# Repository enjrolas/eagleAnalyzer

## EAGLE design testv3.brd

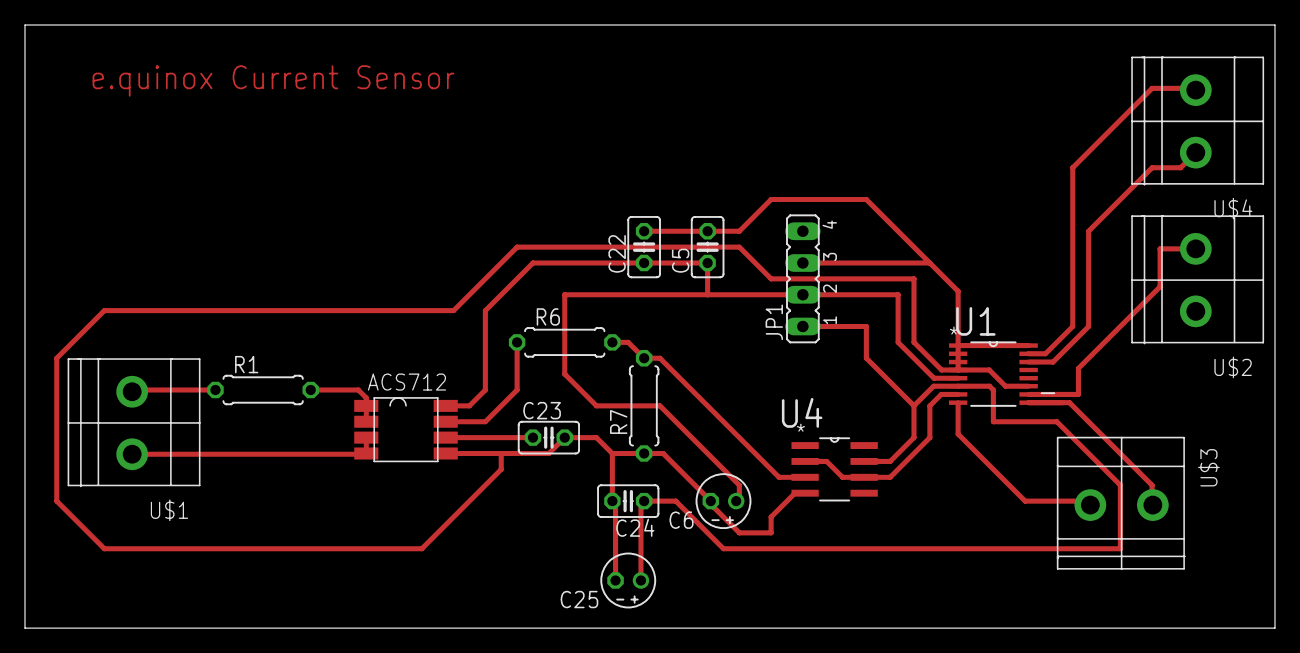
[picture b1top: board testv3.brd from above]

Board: 2 copper layers, 100.0 x 48.2 mm, 17 parts (0 on the bottom side), 15 nets.

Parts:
C5, C22, C23, C24: C025-025X050
C6, C25: E2-4
JP1: JP4
R1, R6, R7: 0207/7
U1: AD7993BRUZ-0; SOP65P640X120-16N
U4: MCP601-E/SN; SOIC127P600X175-8N
U$1, U$2, U$3, U$4: CTB1500/2; CTB1500-2
U$10: ACS712; SOIC8

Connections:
+3V3: C24.1, C25.+, JP1.1, U1.6, U4.7
+5V: C5.1, C6.+, C22.1, JP1.2, U1.5, U$10.8
GND: C5.2, C6.-, C22.2, C23.2, C24.2, C25.-, JP1.3, R7.1, U1.1, U1.2, U1.3, U1.4, U1.11, U1.16, U4.4, U$10.5
IDC_OUT: U1.7, U4.2, U4.6
unnamed: U1.9, U$3.P$1
unnamed: U1.8, U$3.P$2
unnamed: R1.1, U$1.P$2
unnamed: R1.2, U$10.1, U$10.2
unnamed: U$1.P$1, U$10.3, U$10.4
unnamed: R6.1, U$10.7
unnamed: C23.1, U$10.6
unnamed: R6.2, R7.2, U4.3
unnamed: U1.14, U$4.P$1
SCL: U1.15, U$4.P$2
VDC_OUT: U1.10, U$2.P$2

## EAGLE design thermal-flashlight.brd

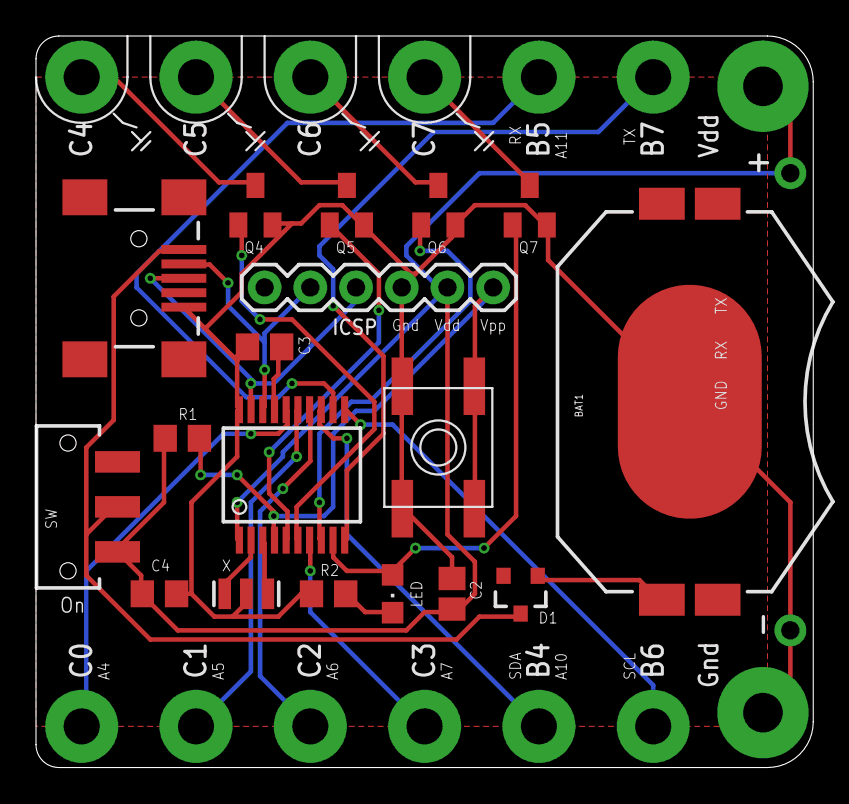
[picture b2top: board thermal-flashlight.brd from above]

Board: 2 copper layers, 43.2 x 40.6 mm, 34 parts (0 on the bottom side), 27 nets.

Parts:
BAT1: BATTCON_20MM_4LEGS
BTN: EVQ-Q2
C2: 10u; C0805
C3, C4: 0.1uF; C0805
D1: SOT23-3
ICSP: 1X06
JP+: 1X01-CLEANBIG
JP-: 1X01-CLEANBIG
LED: 0805; CHIPLED_0805
PB4: PETAL-SMALL-2SIDE1
PB5, PB6, PB7: SEWTAP6; PETAL-SMALL-2SIDE1
PC0, PC1, PC2, PC3: SEWTAP6; PETAL-SMALL-2SIDE1
PG: SEWTAP6; PETAL-SMALL-2SIDE11
PSC4, PSC5, PSC6, PSC7: SEWTAP6; PETAL-SMALL-2SIDE1
PVCC: SEWTAP6; PETAL-SMALL-2SIDE11
Q4, Q5, Q6, Q7: BSS123; SOT23
R1: 10k; R0805@1
R2: 3.3K; R0805
SW: SPDT; SWITCH-SPDT-SMD
U$1: PIC18F1X50-I/SS; SSOP20
X: 12MHz; RESONATOR-SMD
X1: USBSMD; USB-MINIB

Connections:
GND: BAT1.2, BTN.A, BTN.A', C2.2, C3.2, C4.2, ICSP.3, JP-.1, PG.1, Q4.2, Q5.2, Q6.2, Q7.2, R2.1, U$1.20, X.2, X1.GND
unnamed: U$1.2, X.1
unnamed: U$1.3, X.3
unnamed: LED.C, R2.2
PGC: ICSP.5, U$1.18, X1.D-
PGD: ICSP.4, U$1.19, X1.D+
RB4: PB4.1, U$1.13
RB5: PB5.1, U$1.12
RB6: PB6.1, U$1.11
RB7: PB7.1, U$1.10
RC0: PC0.1, U$1.16
RC1: PC1.1, U$1.15
RC2: PC2.1, U$1.14
RC3: PC3.1, U$1.7
RC4: Q4.1, U$1.6
RC5: Q5.1, U$1.5
RC6: Q6.1, U$1.8
RC7: LED.A, Q7.1, U$1.9
SC4: PSC4.1, Q4.3
SC5: PSC5.1, Q5.3
SC6: PSC6.1, Q6.3
SC7: PSC7.1, Q7.3
VBAT: BAT1.1, D1.1
VBUS: D1.3, SW.2, X1.VBUS
VDD: C2.1, C4.1, ICSP.2, JP+.1, PVCC.1, R1.2, SW.1, U$1.1
VPP: BTN.B, BTN.B', ICSP.1, R1.1, U$1.4
VUSB: C3.1, U$1.17

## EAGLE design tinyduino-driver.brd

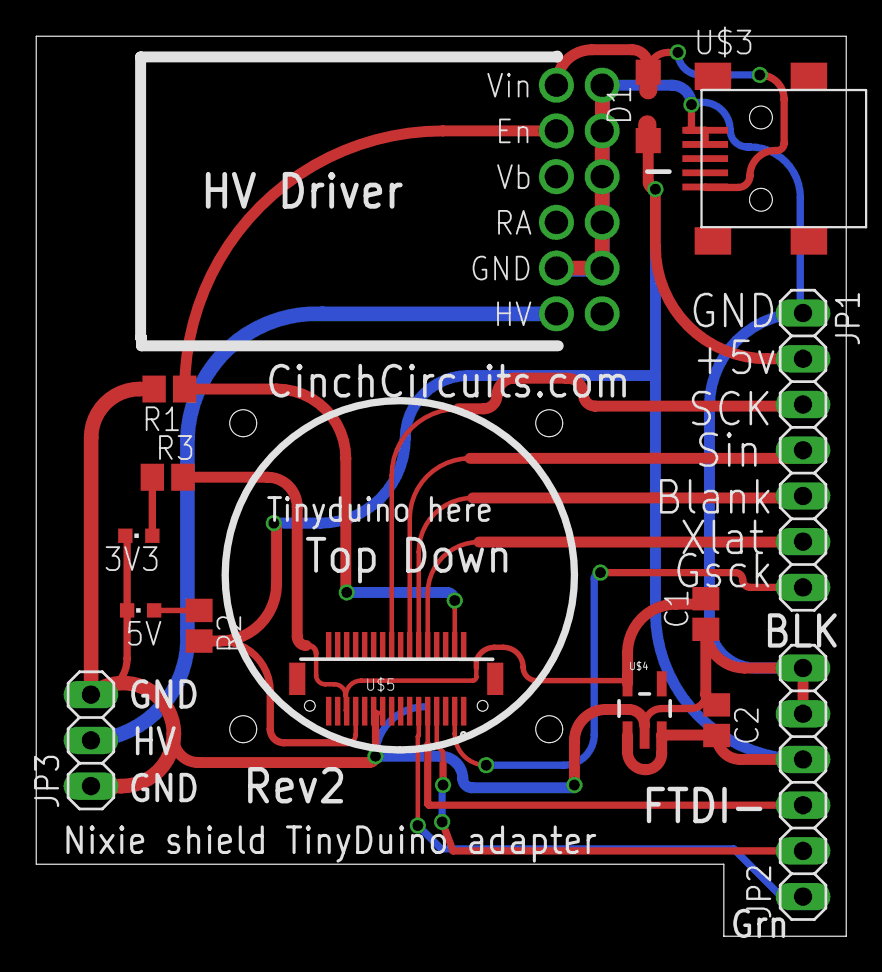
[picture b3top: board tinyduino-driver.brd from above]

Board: 2 copper layers, 45.0 x 50.0 mm, 16 parts (0 on the bottom side), 16 nets.

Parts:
3V3, 5V: CHIPLED_0603
C1, C2: C0805
D1: MBR0520LT; SOD123
JP1: 1X07
JP2: 1X06
JP3: 1X03
R1: 10k; R0805
R2, R3: R0805
U$1: DOCFIELD-TINYCIRCUITS-PCB
U$2: HV-MODULE-EBAY; NIIE-HV
U$3: USB-MICRO-SMD; CONNECTER_MINI_USB2
U$4: 3V3-LDO-TI; SOT23-5
U$5: TINYCIRCUITS-DF12-32-DS-BOTTOM; TINYCIRCUITS_DF12-32-DS

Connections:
+3V3: C1.2, R3.2, U$4.5, U$5.27
+5V: C2.2, D1.C, JP1.2, JP2.4, R2.2, U$4.1, U$4.3, U$5.25
GND: 3V3.C, 5V.C, C1.1, C2.1, JP1.1, JP2.5, JP2.6, JP3.1, JP3.3, R1.2, U$2.GND, U$2.GND1, U$2.GND2, U$2.GND4, U$2.GND5, U$2.GND6, U$3.GND0, U$3.GND1, U$4.2, U$5.19, U$5.21
HVOUT: JP3.2, U$2.HV
IO0: JP2.3, U$5.9
IO1: JP2.2, U$5.7
IO3: JP1.7, U$5.3
IO6: R1.1, U$2.ENABLE, U$5.4
IO9: JP1.6, U$5.10
MOSI: JP1.4, U$5.14
unnamed: 3V3.A, R3.1
unnamed: 5V.A, R2.1
RESET: JP2.1, U$5.11
SCK: JP1.3, U$5.18
SS: JP1.5, U$5.12
USB+5V: D1.A, U$2.VIN, U$3.VDD

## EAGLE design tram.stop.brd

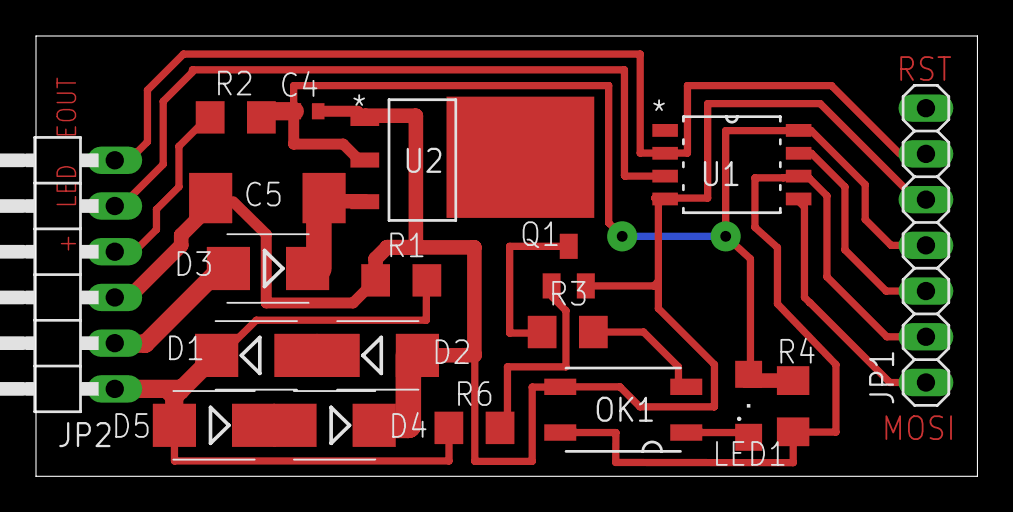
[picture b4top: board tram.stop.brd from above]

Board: 2 copper layers, 52.3 x 24.5 mm, 19 parts (0 on the bottom side), 18 nets.

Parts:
C4: 1uF; C0402
C5: SMC_D
D1, D2, D3, D4, D5: M1; SMB
JP1: 1X07
JP2: 1X06/90
LED1: KPT-3216SRD-PRV; SML1206
OK1: PC357N14; SMD4
Q1: BC847SMD; SOT23
R1: 2k2; R1206
R2, R3: 220; R1206
R4: 10K; R1206
R6: 1K; R1206
U1: ATTINY85V-10SU; SOIC127P798X216-8N
U2: LM1117MP-5.0; SOT230P696X180-4N

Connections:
220: LED1.C, OK1.1
JP1: D3.C, D5.A, JP2.1, R1.1, R6.1
JP2: C4.2, D2.A, D4.C, JP1.5, JP2.3, OK1.3, Q1.2, R1.2, U1.4, U2.1
unnamed: D2.C, D3.A
unnamed: D4.A, D5.C
unnamed: Q1.1, R6.2
unnamed: Q1.3, R3.1
unnamed: OK1.2, R3.2
unnamed: JP1.3, U1.7
unnamed: JP1.1, U1.5
unnamed: JP2.4, R2.1
unnamed: JP1.6, JP2.6
unnamed: JP1.2, OK1.4, R4.1, U1.6
unnamed: C4.1, JP1.4, LED1.A, R2.2, R4.2, U1.8, U2.2
unnamed: JP1.7, U1.1
unnamed: D1.A, JP2.2
unnamed: C5.+, D1.C, U2.3
RED2: JP2.5, U1.3

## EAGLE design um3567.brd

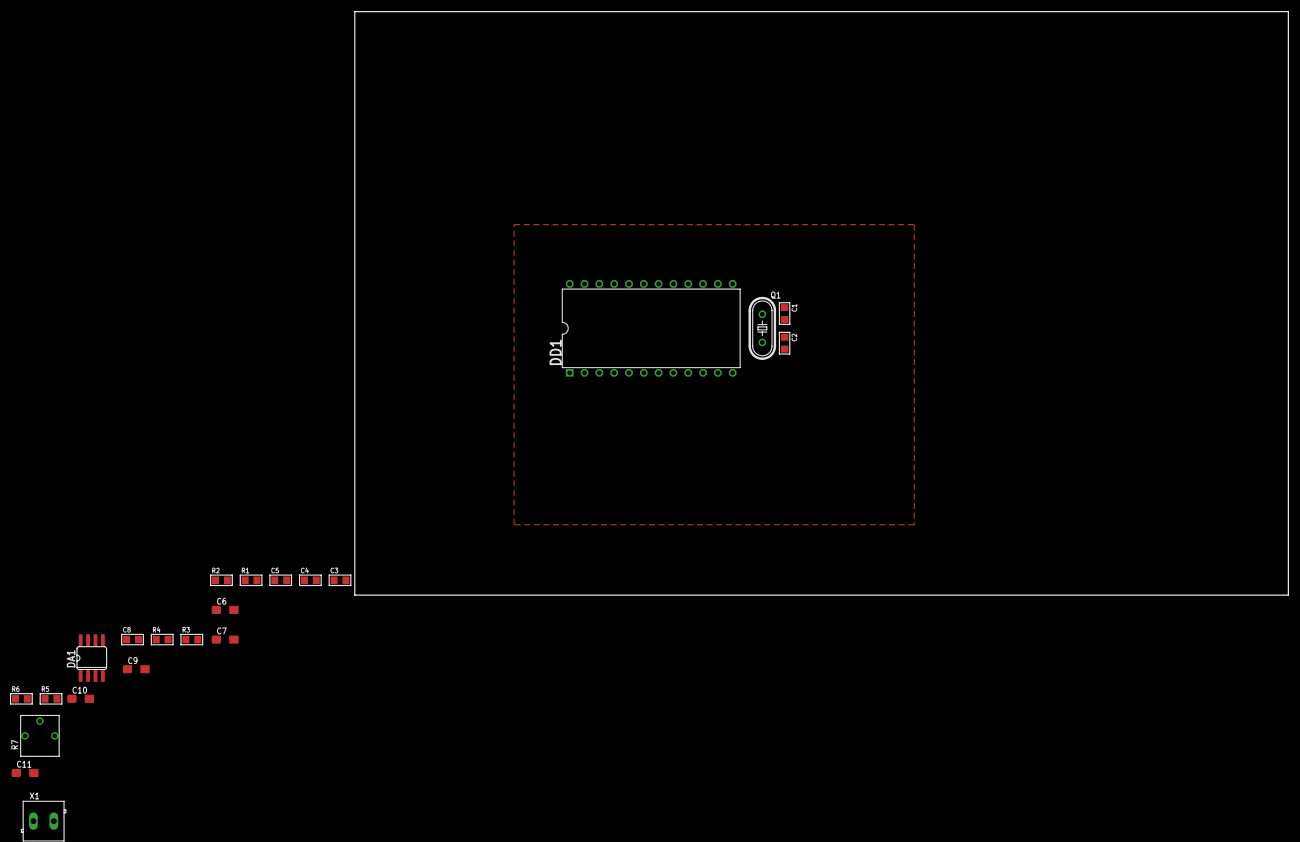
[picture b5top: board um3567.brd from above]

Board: 2 copper layers, 160.0 x 100.0 mm, 22 parts (0 on the bottom side), 17 nets, no tracks yet.

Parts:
C1, C2: 30pF; C0805
C3, C4, C5: 0.1; C0805
C6, C7, C10, C11: 1uF; SMC_A
C8: 10n; C0805
C9: 10uF; SMC_A
DA1: LM4871MX; SO08
DD1: UM3567; DIL24
Q1: 3.579545 MHz; HC49/S
R1, R2: 4.7K; R0805
R3, R4: 22K; R0805
R5, R6: 20K; R0805
R7: 100K; RTRIM-3362P
X1: DG3XX-02-3.5; DG350-3.5-02P

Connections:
GND: C1.2, C2.2, C3.2, C4.2, C5.2, C8.2, C10.-, C11.-, DA1.7, DD1.1, R3.1, R7.3
unnamed: C1.1, DD1.10, Q1.1
unnamed: C2.1, DD1.11, Q1.2
unnamed: DD1.19, R1.1
unnamed: DD1.18, R2.1
unnamed: C6.-, C7.+, R2.2
unnamed: C6.+, R1.2
unnamed: C7.-, R3.2, R4.1
unnamed: C8.1, C9.+, R4.2
unnamed: C10.+, DA1.6
unnamed: DA1.4, R5.1, R6.2
unnamed: DA1.5, R5.2, X1.1
unnamed: C9.-, R7.1
unnamed: R6.1, R7.2
unnamed: C11.+, DA1.2, DA1.3
unnamed: DA1.8, X1.2
VCC: C3.1, C4.1, C5.1, DD1.21

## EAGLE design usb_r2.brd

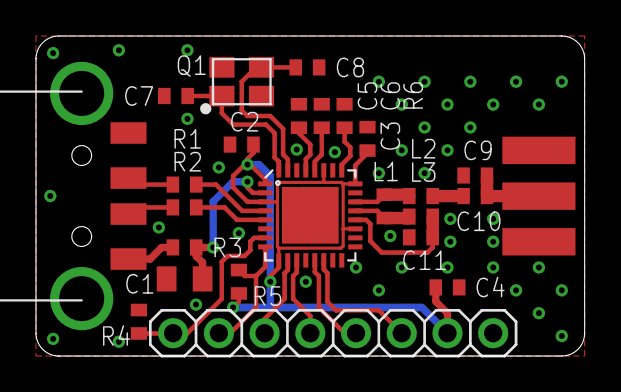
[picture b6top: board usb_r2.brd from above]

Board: 2 copper layers, 30.5 x 17.8 mm, 25 parts (0 on the bottom side), 24 nets.

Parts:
C1: 10uF; C0805K
C2, C3, C4: 10nF; C0402
C5, C6: 33nF; C0402
C7, C8: 27pF; C0402
C9: 1.2pF; C0402
C10: 1pF; C0402
C11: 2.2nF; C0402
J$1: SMA_EDGE; SMA-EDGE
JP1: 1X08
L1, L3: 6.8nH; C0402
L2: 4.7nH; C0402
Q1: 16MHz; TSX-3225
R1, R2: 22R; R0402
R3: 10R; R0402
R4, R5: 10K; R0402
R6: 22K; R0402
U$1: NRF24LU1; QFN-32
X1: USB-A; MOLEX_480371000

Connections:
CS: JP1.6, U$1.14
GND: C1.2, C2.2, C3.2, C4.2, C5.1, C6.1, C7.1, C8.1, C10.2, C11.2, J$1.GND@0, J$1.GND@1, J$1.GND@2, J$1.GND@3, JP1.8, Q1.2, Q1.4, R4.1, R6.1, U$1.6, U$1.12, U$1.17, U$1.18, U$1.23, U$1.26, U$1.30, X1.4
MISO: JP1.5, U$1.13
MOSI: JP1.4, U$1.11
unnamed: R1.1, X1.3
unnamed: R2.1, X1.2
unnamed: R1.2, U$1.4
unnamed: R2.2, U$1.5
unnamed: C5.2, U$1.29
unnamed: R3.1, X1.1
unnamed: C1.1, R3.2, U$1.2
unnamed: C6.2, U$1.28
unnamed: R6.2, U$1.25
unnamed: C8.2, Q1.3, U$1.31
unnamed: C7.2, Q1.1, U$1.32
unnamed: C9.1, L2.2
unnamed: C9.2, C10.1, J$1.SIG
unnamed: L1.1, L2.1, U$1.22
unnamed: C11.1, L3.2, U$1.20
unnamed: L1.2, L3.1, U$1.21
PROG: JP1.1, R4.2, U$1.7
RESET: JP1.2, R5.2, U$1.8
SCK: JP1.3, U$1.10
VDD: C2.1, C3.1, C4.1, JP1.7, R5.1, U$1.1, U$1.3, U$1.9, U$1.19, U$1.24, U$1.27

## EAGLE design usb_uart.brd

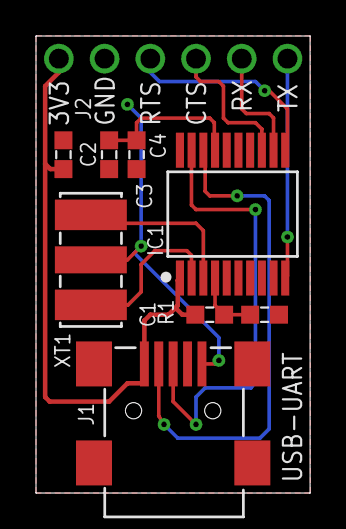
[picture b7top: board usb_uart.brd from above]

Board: 2 copper layers, 15.2 x 25.4 mm, 9 parts (0 on the bottom side), 12 nets.

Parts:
C1, C2, C3, C4: 0.1uF; CAPC0603
IC1: SOP65P775X200-20M
J1: USB-MINIB-SMD+SMD+RET
J2: PHSP254P1524X254X1154-6S
R1: 10k; RESC0603
XT1: 12MHz; CERAMIC740X340-3N

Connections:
+3V3: C1.1, C2.1, IC1.1, J1.1, J2.1
CTS: IC1.13, J2.4
GND: C2.2, C3.2, C4.2, IC1.20, J1.5, J2.2, R1.P$1, XT1.2
unnamed: IC1.2, XT1.1
unnamed: IC1.3, XT1.3
unnamed: C1.2, IC1.4, R1.P$2
unnamed: IC1.19, J1.3
unnamed: IC1.18, J1.2
unnamed: C3.1, C4.1, IC1.17
RTS: IC1.11, J2.3
RX: IC1.12, J2.5
TX: IC1.10, J2.6

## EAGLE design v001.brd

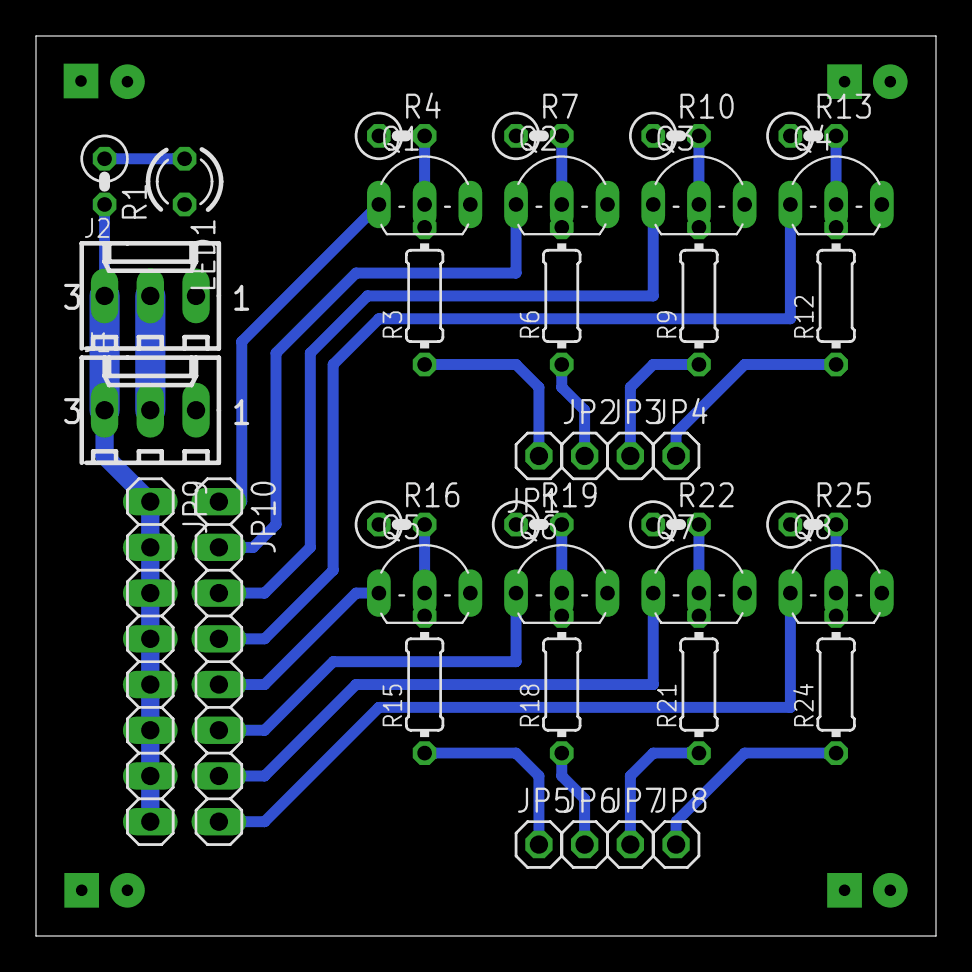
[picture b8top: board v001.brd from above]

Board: 2 copper layers, 50.0 x 50.0 mm, 39 parts (0 on the bottom side), 28 nets.

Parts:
J1: Pwr-1; 6410-03
J2: Pwr-2; 6410-03
JP1: In-1; 1X01
JP2: In-2; 1X01
JP3: In-3; 1X01
JP4: In-4; 1X01
JP5: In-5; 1X01
JP6: In-6; 1X01
JP7: In-7; 1X01
JP8: In-8; 1X01
JP9: 12V; 1X08
JP10: Outputs; 1X08
LED1: Green; LED3MM
PCB1: ZZZ_MODULE05X05; ZZZ_MODULE_05X05
Q1, Q2, Q3, Q4, Q5, Q6, Q7, Q8: BC548; TO92-EBC
R1: 1K; 0207/2V
R3, R6, R9, R12, R15, R18, R21, R24: 2K2; 0204/7
R4, R7, R10, R13, R16, R19, R22, R25: 10K; 0207/2V

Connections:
+5V: J1.2, J2.2
+12V: J1.3, J2.3, JP9.1, JP9.2, JP9.3, JP9.4, JP9.5, JP9.6, JP9.7, JP9.8, R1.2
GND: J1.1, J2.1, LED1.K, PCB1.GND@1, PCB1.GND@2, PCB1.GND@3, PCB1.GND@4, PCB1.GND@5, PCB1.GND@6, PCB1.GND@7, PCB1.GND@8, Q1.E, Q2.E, Q3.E, Q4.E, Q5.E, Q6.E, Q7.E, Q8.E, R4.1, R7.1, R10.1, R13.1, R16.1, R19.1, R22.1, R25.1
unnamed: LED1.A, R1.1
unnamed: Q2.B, R6.2, R7.2
unnamed: JP2.1, R6.1
unnamed: Q3.B, R9.2, R10.2
unnamed: JP3.1, R9.1
unnamed: Q4.B, R12.2, R13.2
unnamed: JP4.1, R12.1
unnamed: Q5.B, R15.2, R16.2
unnamed: JP5.1, R15.1
unnamed: Q1.B, R3.2, R4.2
unnamed: JP1.1, R3.1
unnamed: Q6.B, R18.2, R19.2
unnamed: JP6.1, R18.1
unnamed: Q7.B, R21.2, R22.2
unnamed: JP7.1, R21.1
unnamed: Q8.B, R24.2, R25.2
unnamed: JP8.1, R24.1
OUTPUT-1: JP10.1, Q1.C
OUTPUT-2: JP10.2, Q2.C
OUTPUT-3: JP10.3, Q3.C
OUTPUT-4: JP10.4, Q4.C
OUTPUT-5: JP10.5, Q5.C
OUTPUT-6: JP10.6, Q6.C
OUTPUT-7: JP10.7, Q7.C
OUTPUT-8: JP10.8, Q8.C

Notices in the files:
tinyduino-driver.brd:
Released under the Creative Commons Attribution Share-Alike 3.0 License
http://creativecommons.org/licenses/by-sa/3.0
parts and their libraries:
rc-master-smd: Copyright (C) 2007, Bob Starr
SparkFun: Licensing: CC v3.0 Share-Alike You are welcome to use this library for commercial purposes.
